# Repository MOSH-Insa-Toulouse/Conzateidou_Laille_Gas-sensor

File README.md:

# Conzateidou_Laille_Gas-sensor
Julie CONZATEIDOU 5 ISS A1 - David LAILLE 5 ISS B1

<h1>Smart gas sensor - Data acquisition device</h1>

<p>As part of the Innovative Smart System Master at INSA of Toulouse, we have to design a smart and connected gas sensor. Our project is divided into three parts. The first one consists in fabricating the gas sensor. That will be done during a session at AIME, in a few time. The second one is the communication part, which will be implemented by using LoRa modules. The last one is the realisation of a shield able to link the gas sensor and a microcontroller, an Arduino Uno card. That one will do the analysis en the transmission of data.
The design of the de data acquisition component has been realised with the software KiCad. It is composed of three main steps. First, we create, the schematic of the circuit that we want to fabricate. With that, we can simulate the behaviour of our circuit and check electrical connections.Then, we combine every component with the corresponding print. Finally, we make the routing of the card by drawing conductive track to link all the components on the same layer.
In the following parts, we will explain more precisely the organisation of the data acquisition device, and also the different steps to design it.
</p>

<h3>Functionalities</h3>
	<p>The circuit is composed of one instrumentation amplifier, made using AOP (LTC1050), one Arduino Uno card and one shield enabling the connection with LoRa module (RN2483).
	The instrumentation amplifier collect data from the gas sensor, amplify them to make them readable, and transmit them on analog pin A0. The pin A0 has been chosen randomly, so we could also use the other analog pins.
	The gas sensor is powered by 3.3V. The signal from the sensor is filtered with a RC circuit and then amplified (by around 100 in this case). The output of the AOP is also filtered with an other RC circuit. The power supply of the AOP (5V) can introduce some noise, so we add a capacitor to avoid the noise caused by this power supply.
	The circuit we have done is shown below.</p>

<h3>Content</h3>
<p>In this git, you will find :
<ul>
<li>the electrical schematic of the circuit<il>
<li>the netlist<il>
<li>the PCB with routing<il>  </ul>
</p>

<h3>Choices for design</h3>
<p>We did not make the routing of the shield, in order to keep a device compact and not too large. Thereafter, we could weld the shield with the card.
</p>

<h3>Realization</h3>
<p>Below, we can see the PCB with the routing. we represented the shield for LoRa on this picture to have an overview of the device, even if the module is not connected.
</p>

With 3D viewing, we can see what could be done in real.

<h3>Analysis</h3>
<p>The major difficulty we encountered during the project was the design of the PCB. With the constraint of using only one layer, a lot of tracks were overlapping, and that made the routing harder. We had to work a lot on the layout of the components.
The conductive tracks are quite thin. Larger tracks could be more appropriate.</p>

<h3>Possible improvements</h3>
<p>The device is a simple data acquisition module. Afterwards in the project, we will add and program a LoRa module to be able to collect data from the gas sensor. These data could be sent, after, on a database like The Things Network to analyze and display them. With that improvement we could be able to follow the evolution of gas concentrations, remotely and in real-time. Another improvement could be the addition of a battery to make the device more autonomous, or by using solar plans.
</p>

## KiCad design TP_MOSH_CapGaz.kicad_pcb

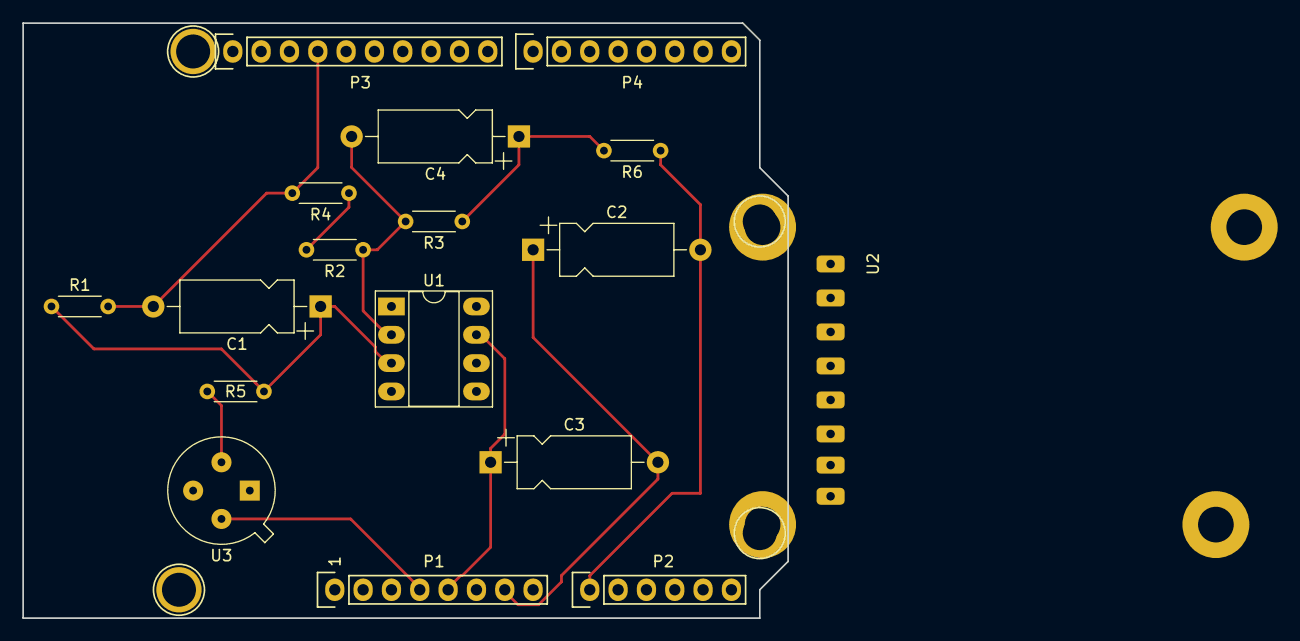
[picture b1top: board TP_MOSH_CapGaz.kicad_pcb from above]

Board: 2 copper layers, 68.6 x 53.3 mm, 21 parts (0 on the bottom side), 10 nets.

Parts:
C1, C2, C3: 100n; CP_Axial_L10.0mm_D4.5mm_P15.00mm_Horizontal
C4: 1u; CP_Axial_L10.0mm_D4.5mm_P15.00mm_Horizontal
P1: Power; Socket_Strip_Arduino_1x08
P2: Analog; Socket_Strip_Arduino_1x06
P3: Digital; Socket_Strip_Arduino_1x10
P4: Digital; Socket_Strip_Arduino_1x08
P5, P6, P7, P8: CONN_01X01; Arduino_1pin
R1, R3: 100k; R_Axial_DIN0204_L3.6mm_D1.6mm_P5.08mm_Horizontal
R2, R6: 1k; R_Axial_DIN0204_L3.6mm_D1.6mm_P5.08mm_Horizontal
R4: 220; R_Axial_DIN0204_L3.6mm_D1.6mm_P5.08mm_Horizontal
R5: 10k; R_Axial_DIN0204_L3.6mm_D1.6mm_P5.08mm_Horizontal
U1: LTC1050; DIP-8_W7.62mm_Socket_LongPads
U2: RN2483; Module_RN2483_Breakout
U3: Gas_sensor; TO-5-4

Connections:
+3V3: P1.4, U2.6, U3.4
+5V: C3.1, P1.5, U1.7
/A0: C2.2, P2.1, R6.1
/Reset: P1.3, U2.5
GND: C1.2, C2.1, C3.2, P1.6, P1.7, P3.4, R1.2, R4.2, U1.4, U2.8
unnamed: C1.1, R1.1, R5.2, U1.3
unnamed: C4.1, R3.1, R6.2, U1.6
unnamed: C4.2, R2.1, R3.2, U1.2
unnamed: R2.2, R4.1
unnamed: R5.1, U3.2

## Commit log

2018-11-30 Init
2018-11-30 README
2018-11-30 wrong extension
2018-11-30 Add image
